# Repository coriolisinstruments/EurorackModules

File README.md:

# EurorackModules

Open-source eurorack synthesizer modules. All our schematics and pcbs are developed with [KiCad.](http://kicad.org/)

## 1U modules

These are simple (passive) utility modules, designed to fit the Intellijel 1U spec. They are often smaller (6 or 8HP) so you can use them to fill gaps in your system. Except for the Multibus... that one takes up an entire row.

| | Module | Description |
| --- | :----- | :---------- |
|| [LPG](1Utilities/1U_LPG) | A simple passive low-pass gate with -6dB slope in a small 1U package. |
|| [Mute](1Utilities/1U_Mute) | A signal mute (momentary and latching) in a convenient 1U package.|
|| [Mult](1Utilities/1U_Mult) | Dead simple passive multi. Its only feature being very small. |
|| [Multibus](Multibus) | A eurorack module for the distribution of CV signals. |

## Regular (3U) Modules

Just your regular sized eurorack modules.

| | Module | Description |
| --- | :----- | :---------- |
|| [Corona](Corona) | A multi purpose vacuum tube (or valve) drive module with feedback control. |

## Other stuff
| | Thing | Description |
| --- | :----- | :---------- |
|| [PSU Companion](PSUCompanion) | A companion for Bel / Condor / Power One linear power supplies. Goes inbetween the PSU and your busboards. |
|| [Making Vactrols](MakingVactrols) | A little tutorial on making your own vactrols. |

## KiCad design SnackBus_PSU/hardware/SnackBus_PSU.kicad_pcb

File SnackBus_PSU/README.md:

# SnackBus PSU

A small, easy to DIY, power supply for Eurorack modules. Designed to be used in a surplus Moog Mother-32 or DFAM skiff, utilizing the existing wall-wart and internal connector. Add some spacers as feet and you can also use it as a benchtop power supply for your eurorack breadboarding experiments.

*status:* build and tested

*current revision:* 2

## About

This power supply was design as a even lower-cost (the total cost is about €30), even smaller, alternative to the excellent Befaco LunchBus skiff PSU. In terms of circuitry, the SnackBus is almost identical. Why use this? Well, the SnackBus fits into a Moog 60 HP skiff (from the Mother-32 or DFAM), whereas the LunchBus does not.

## On power output

The DKE15A-12 converter used is capable of delivering 625mA on both +12V and -12V (a total of 1250mA). When it does so, it required 1.7A @12V (20.4W) from the wall-wart.

Note that the Moog adapter, supplied with the Mother-32 and DFAM, will only put out 1A @12V. This means that if you use this adapter, the SnackBus will only be able to output 350mA on both rails. Less if you use 

**Our recommendation: do not exceed 300mA power draw** on either rails when using the Moog-supplied adapter with the SnackBus. Otherwise buy a beefier adapter.

## BOM

| Component | Quantity    | Component     |
| :------------- | :------------- | :------------- |
| R1 | 1 | 680R ohm resistor (for +5V in LED) |
| R2 | 1 | 1k ohm resistor (for -12V LED) |
| R3 | 1 | 1k ohm resistor (for +12V LED) |
| R4 | 1 | 5k ohm resistor (for PWR IN LED) |
| R5 | 1 | 1K ohm resistor (for 5V) |
| R6 | 1 | 330R ohm resistor (for 5V) |
| D1 | 1 | 1N5402 diode |
| D2 | 1 | 1N4004 diode |
| C1 | 1 | Capacitor (ceramic or film) , 100nF (104) |
| C2 | 1 | Capacitor, Polarized (electrolytic) , 10uF |
| C3 | 1 | Capacitor, Polarized (electrolytic) , 22uF |
| J1 | 1 | 2-pin Molex connector |
| J2-J9 | 8 | 16-pin (02x08) Shrouded IDC header |
| U1 | 1 | LM317T voltage regulator |
| M1 | 1 | MeanWell DKE15A-12 DC-DC converter |

All resistors 1% metal film.

## Building order

By no means a build guide; just a suggested order to make building easier.

1. Start soldering with the resistors.
2. Then the diodes.
3. Add the shrouded box headers. Use something flat to keep them in place when you flip the board around.
4. Do the C1 capacitor next.
5. Bend the leads of the LM317T 90 degrees down (the heatsink being the downside of the regulator) where the leads become thinner. Make sure the hole in the tab and on the board align. Add the regular by soldering the leads and screwing the tab to the board with an M3 bolt and nut.
6. Add the LEDs. Use a piece of masking tape the keep them in place.
7. Drop in the regular, flip the board and solder it from the backside.
8. Add the polarized caps C2 and C3.
9. Finally, add J1: the Molex connector. Using a piece of masking tape to fixate it on the board is recommended.

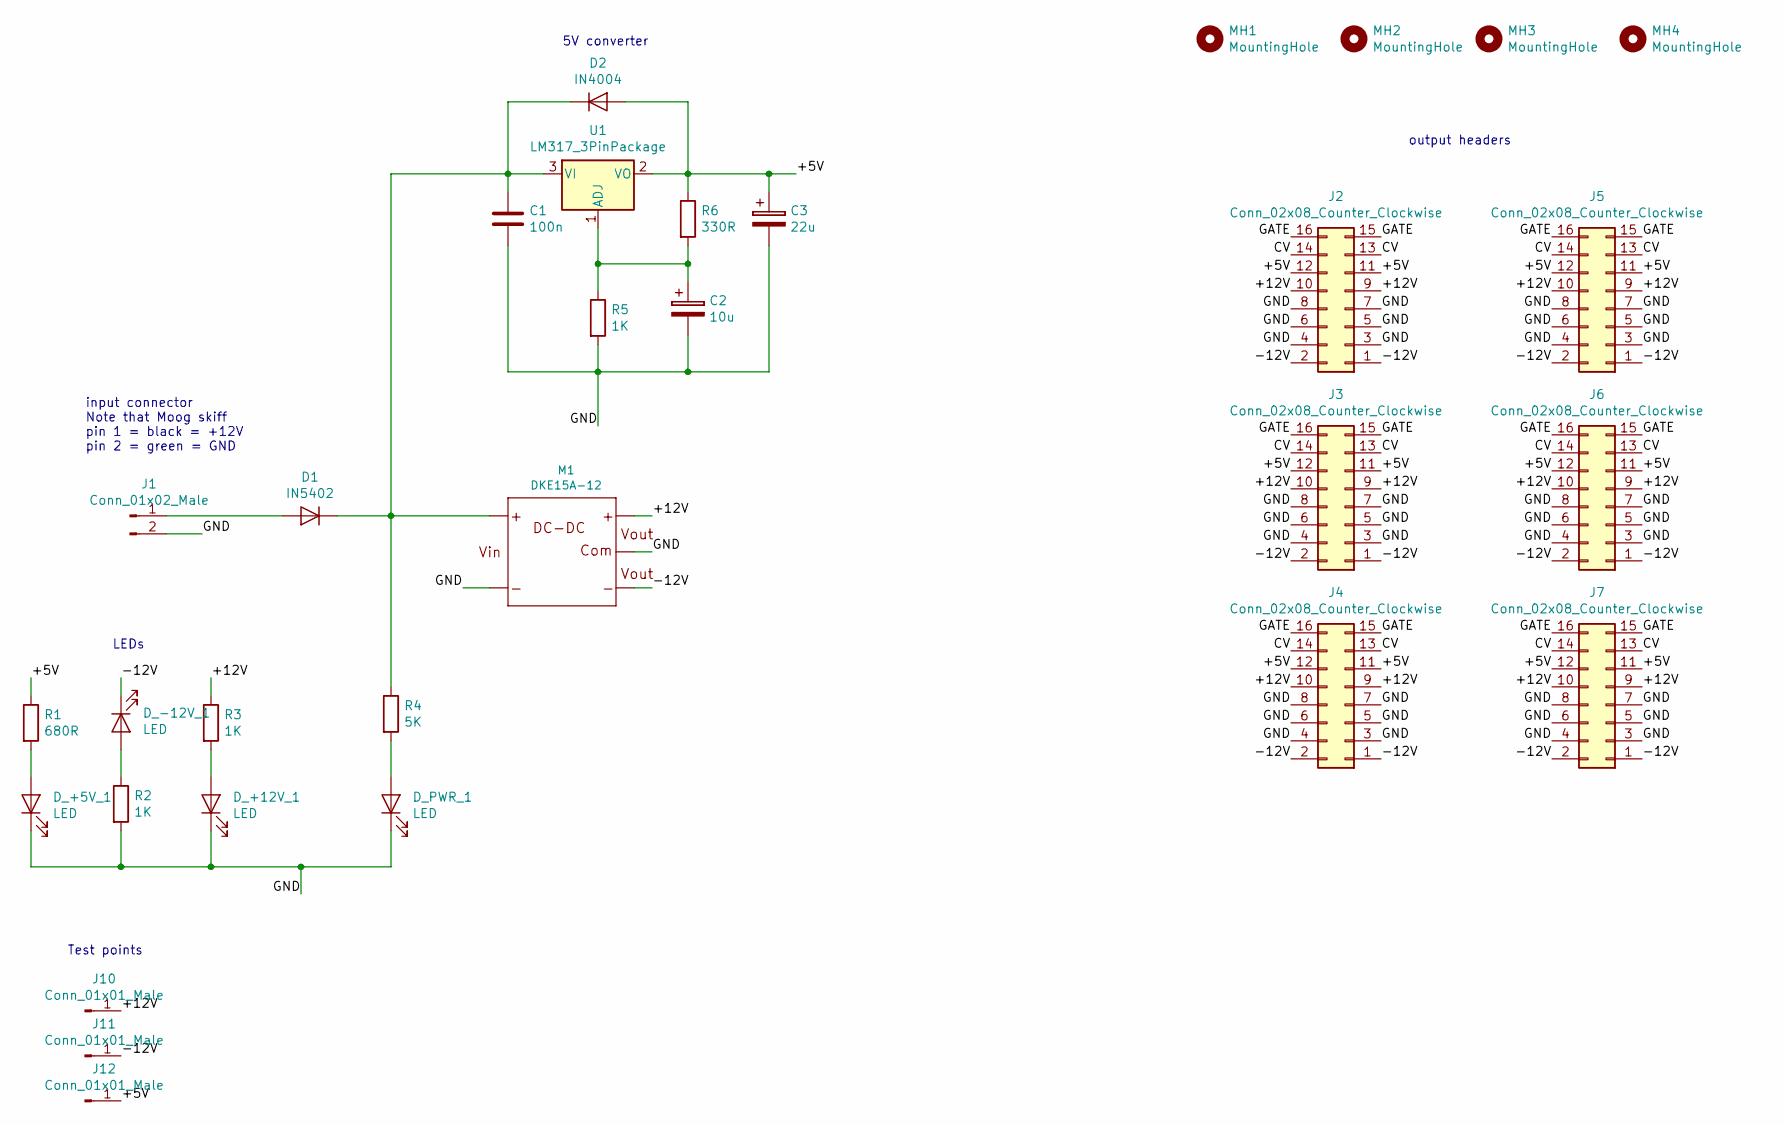
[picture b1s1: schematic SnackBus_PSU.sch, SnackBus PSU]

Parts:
C1: 100n; C_Disc_D7.0mm_W2.5mm_P5.00mm
C2: 10u; CP_Radial_D5.0mm_P2.50mm
C3: 22u; CP_Radial_D5.0mm_P2.50mm
D1: IN5402; D_DO-201AD_P15.24mm_Horizontal
D2: IN4004; D_DO-41_SOD81_P10.16mm_Horizontal
D_+5V_1, D_+12V_1: LED; LED_D3.0mm
D_-12V_1: LED; LED_D3.0mm
D_PWR_1: LED; LED_D3.0mm
J1: Conn_01x02_Male; Molex_KK-254_AE-6410-02A_1x02_P2.54mm_Vertical
J2, J3, J4, J5, J6, J7: Conn_02x08_Counter_Clockwise; IDC-Header_2x08_P2.54mm_Vertical
J10, J11, J12: Conn_01x01_Male; PinHeader_1x01_P2.54mm_Vertical
M1: DKE15A-12; MeanWell-DKE
MH1, MH2, MH3, MH4: MountingHole; MountingHole_3.2mm_M3
R1: 680R; R_Axial_DIN0207_L6.3mm_D2.5mm_P7.62mm_Horizontal
R2, R3, R5: 1K; R_Axial_DIN0207_L6.3mm_D2.5mm_P7.62mm_Horizontal
R4: 5K; R_Axial_DIN0207_L6.3mm_D2.5mm_P7.62mm_Horizontal
R6: 330R; R_Axial_DIN0207_L6.3mm_D2.5mm_P7.62mm_Horizontal
U1: LM317_3PinPackage; TO-220F-3_Horizontal_TabDown

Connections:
/+5V: C3.1, D2.2 (A), J2.11, J2.12, J3.11, J3.12, J4.11, J4.12, J5.11, J5.12, J6.11, J6.12, J7.11, J7.12, J12.1, R1.1, R6.1, U1.2 (VO); also elsewhere on the board
/+12V: J2.9, J2.10, J3.9, J3.10, J4.9, J4.10, J5.9, J5.10, J6.9, J6.10, J7.9, J7.10, J10.1, M1.3 (+VOUT), R3.1; also elsewhere on the board
/-12V: D_-12V_1.1 (K), J2.1, J2.2, J3.1, J3.2, J4.1, J4.2, J5.1, J5.2, J6.1, J6.2, J7.1, J7.2, J11.1, M1.5 (-VOUT); also elsewhere on the board
/CV: J2.13, J2.14, J3.13, J3.14, J4.13, J4.14, J5.13, J5.14, J6.13, J6.14, J7.13, J7.14; also elsewhere on the board
/GATE: J2.15, J2.16, J3.15, J3.16, J4.15, J4.16, J5.15, J5.16, J6.15, J6.16, J7.15, J7.16; also elsewhere on the board
/GND: C1.2, C2.2, C3.2, D_+5V_1.1 (K), D_+12V_1.1 (K), D_PWR_1.1 (K), J1.2, J2.3, J2.4, J2.5, J2.6, J2.7, J2.8, J3.3, J3.4, J3.5, J3.6, J3.7, J3.8, J4.3, J4.4, J4.5, J4.6, J4.7, J4.8, J5.3, J5.4, J5.5, J5.6, J5.7, J5.8, J6.3, J6.4, J6.5, J6.6, J6.7, J6.8, J7.3, J7.4, J7.5, J7.6, J7.7, J7.8, M1.2 (-VIN), M1.4 (COMMON), R2.2, R5.2; also elsewhere on the board
unnamed: C1.1, D1.1 (K), D2.1 (K), M1.1 (+VIN), R4.1, U1.3 (VI)
unnamed: C2.1, R5.1, R6.2, U1.1 (ADJ)
unnamed: D1.2 (A), J1.1
unnamed: D_+5V_1.2 (A), R1.2
unnamed: D_+12V_1.2 (A), R3.2
unnamed: D_-12V_1.2 (A), R2.1
unnamed: D_PWR_1.2 (A), R4.2

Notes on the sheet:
output headers
input connector Note that Moog skiff pin 1 = black = +12V pin 2 = green = GND
5V converter
LEDs
Test points

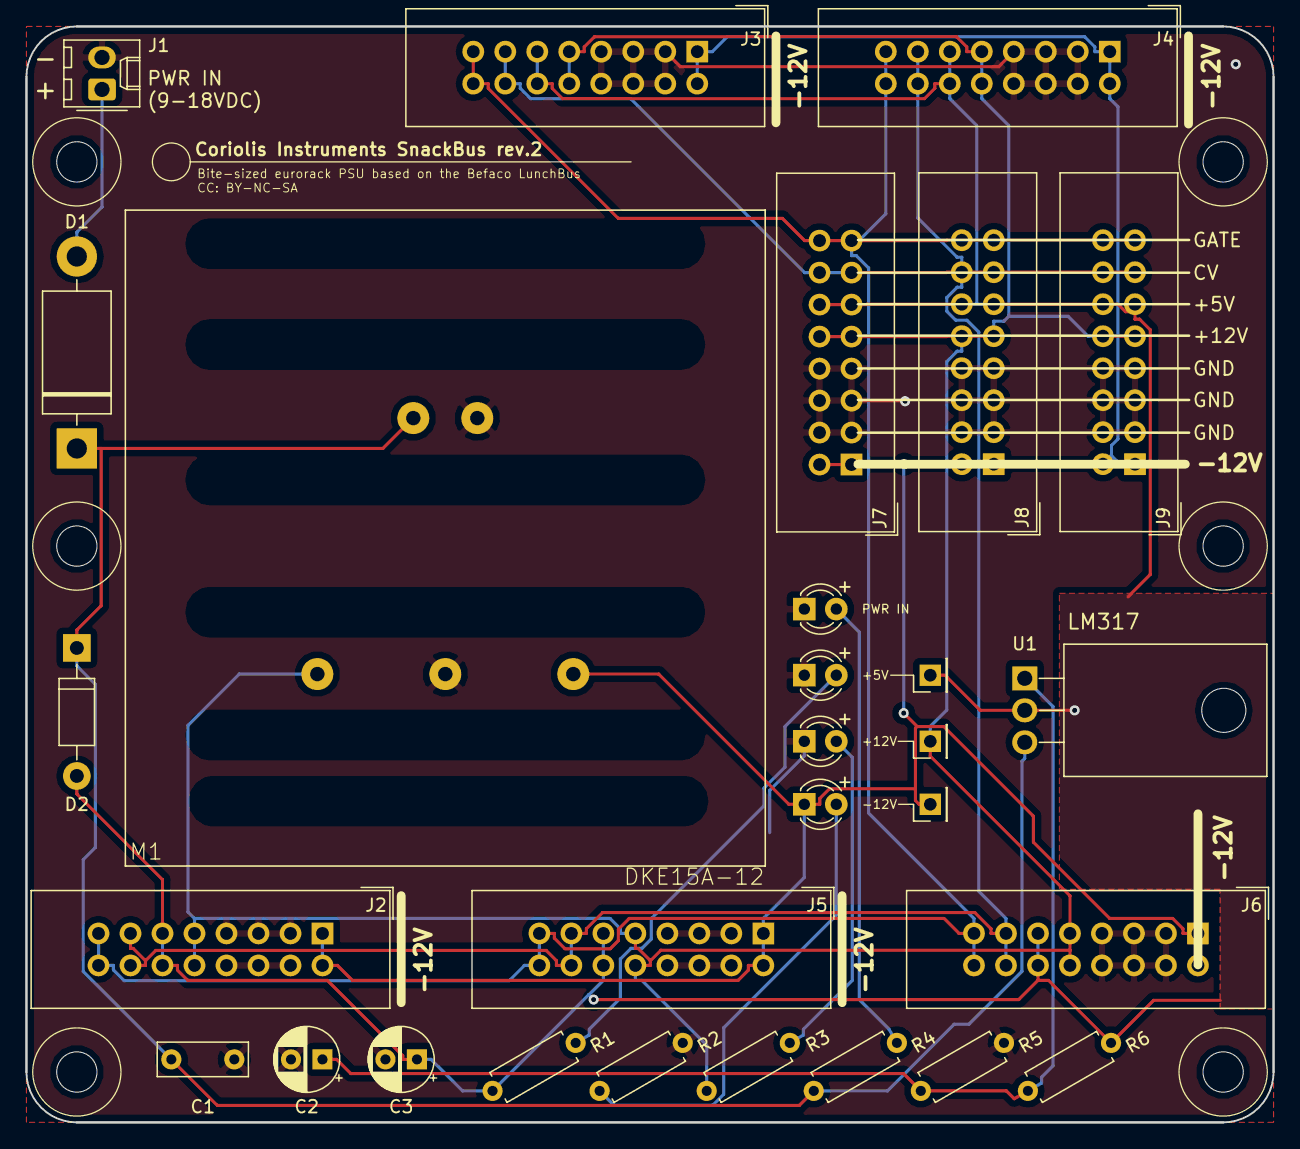
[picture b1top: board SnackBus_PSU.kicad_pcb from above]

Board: 2 copper layers, 99.0 x 87.0 mm, 41 parts (0 on the bottom side), 13 nets.

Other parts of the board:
J8, J9: Conn_02x08_Counter_Clockwise; IDC-Header_2x08_P2.54mm_Vertical
MH5, MH6: MountingHole; MountingHole_3.2mm_M3
SLOT1, SLOT2, SLOT3, SLOT4, SLOT5, SLOT6: mechanical_cooling_slot_very_large

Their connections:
/+5V: J8.11, J8.12, J9.11, J9.12; also elsewhere on the board
/+12V: J8.9, J8.10, J9.9, J9.10; also elsewhere on the board
/-12V: J8.1, J8.2, J9.1, J9.2; also elsewhere on the board
/CV: J8.13, J8.14, J9.13, J9.14; also elsewhere on the board
/GATE: J8.15, J8.16, J9.15, J9.16; also elsewhere on the board
/GND: J8.3, J8.4, J8.5, J8.6, J8.7, J8.8, J9.3, J9.4, J9.5, J9.6, J9.7, J9.8; also elsewhere on the board

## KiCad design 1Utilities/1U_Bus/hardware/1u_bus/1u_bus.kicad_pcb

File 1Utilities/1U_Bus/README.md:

# 1U Bus

Bus for the distribution of CV signals. In essence just a very big passive mult with (active) signal indicators. Basically a simplified DIY Make Noise CV bus clone.

*prototyping*

## About

Like the other modules in the 1Utilities series, this module is designed according to the [Intellijel 1U specification.](https://intellijel.com/support/1u-technical-specifications/). This one spans 104 hp width in your case.

## Remarks

It's big? There's still 4 busses with 4 in- or outputs. Like with a passive mult, any jack can be in or out; **just make sure you have one (1) and only one (!) input.** Having multiple inputs could damage your modules (connecting outputs with outputs).

Even though this module multing is passive, it still requires power to run the signal indicators. Makes for a pretty light show too. The values of the resistors in the design assume Red/Green/Blue/White leds for channels 1 to 4 respectively. You can of course substitute your own led/resistor values to taste!

## BOM

| Component | Quantity    | Component     |
| :------------- | :------------- | :------------- |
| J1 | 1 | 2x5 male header pins (2.54mm pitch), boxed or plain | 
| U1 | 1 | TL074 OpAmp |
| U2-U17 | 16 | Thonkiconn mono jacks |
| C1,C2 | 2 | 10uF (>25V) polarized capacitors |
| C3,C4 | 2 | 100nF capacitors |
| D1,D2 | 2 | 1N4001 diode|
| D_POS_?_? / D_NEG_?_? | 32 | 3mm LEDs (use same color for positive and one for negative) |
| R_Fuse_? | 1 | 10R ohm resistors |
| R_Split_?_1 | 4 | 10k ohm resistors for scaling input signal to indicator |
| R_Split_?_2 | 4 | 1k ohm resistors for scaling input signal to indicator |
| R_LED_1_? | 1 | 1k ohm resistors (depends on LEDs) |
| R_LED_2_? | 1 | 470R ohm resistors (depends on LEDs) |
| R_LED_3_? | 1 | 5k1 ohm resistors (depends on LEDs) |
| R_LED_4_? | 1 | 5k1 ohm resistors (depends on LEDs) |

## Building order

Nothing to see here yet.

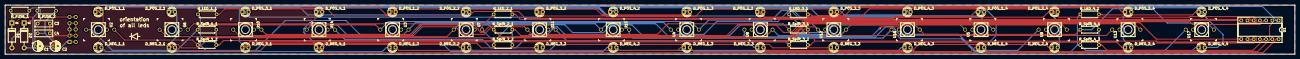
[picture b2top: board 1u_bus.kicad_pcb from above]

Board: 2 copper layers, 526.0 x 20.0 mm, 70 parts (1 on the bottom side), 49 nets.

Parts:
C1, C2: 10uF (25V); CP_Radial_D4.0mm_P2.00mm
C3, C4: 100nF; C_Disc_D7.0mm_W2.5mm_P5.00mm
D1, D2: IN4001; D_DO-41_SOD81_P10.16mm_Horizontal
D_NEG_1_1, D_NEG_1_2, D_NEG_1_3, D_NEG_1_4, D_NEG_2_1, D_NEG_2_2, D_NEG_2_3, D_NEG_2_4, D_NEG_3_1, D_NEG_3_2, D_NEG_3_3, D_NEG_3_4, D_NEG_4_1, D_NEG_4_2, D_NEG_4_3, D_NEG_4_4: LED; LED_D3.0mm
D_POS_1_1, D_POS_1_2, D_POS_1_3, D_POS_1_4, D_POS_2_1, D_POS_2_2, D_POS_2_3, D_POS_2_4, D_POS_3_1, D_POS_3_2, D_POS_3_3, D_POS_3_4, D_POS_4_1, D_POS_4_2, D_POS_4_3, D_POS_4_4: LED; LED_D3.0mm
J1: Conn_02x05_Odd_Even; PinHeader_2x05_P2.54mm_Vertical
R_FUSE_1, R_FUSE_2: 10R; R_Axial_DIN0207_L6.3mm_D2.5mm_P7.62mm_Horizontal
R_LED_1_1: 1K; R_Axial_DIN0207_L6.3mm_D2.5mm_P7.62mm_Horizontal
R_LED_2_1: 470R; R_Axial_DIN0207_L6.3mm_D2.5mm_P7.62mm_Horizontal
R_LED_3_1, R_LED_4_1: 5K1; R_Axial_DIN0207_L6.3mm_D2.5mm_P7.62mm_Horizontal
R_Split_1_1, R_Split_2_1, R_Split_3_1, R_Split_4_1: 10K; R_Axial_DIN0207_L6.3mm_D2.5mm_P7.62mm_Horizontal
R_Split_1_2, R_Split_2_2, R_Split_3_2, R_Split_4_2: 1K; R_Axial_DIN0207_L6.3mm_D2.5mm_P7.62mm_Horizontal
U1: TL074; DIP-14_W7.62mm_Socket
U2, U3, U4, U5, U6, U7, U8, U9, U10, U11, U12, U13, U14, U15, U16, U17: THONKICONNNEW; MusicThingModular-WQP-PJ301M-12_JACK

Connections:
/+12V: C1.1, C3.1, R_FUSE_1.1
/-12V: C2.2, C4.2, R_FUSE_2.1
/GND: C1.2, C2.1, C3.2, C4.1, D1.2, D2.1, J1.3, J1.4, J1.5, J1.6, J1.7, J1.8
/cv_bus1/GND: R_LED_1_1.1, R_Split_1_2.1, U2.P$3_SLEEVE, U3.P$3_SLEEVE, U4.P$3_SLEEVE, U5.P$3_SLEEVE
/cv_bus2/GND: R_LED_2_1.1, R_Split_2_2.1, U6.P$3_SLEEVE, U7.P$3_SLEEVE, U8.P$3_SLEEVE, U9.P$3_SLEEVE
/cv_bus3/GND: R_LED_3_1.1, R_Split_3_2.1, U10.P$3_SLEEVE, U11.P$3_SLEEVE, U12.P$3_SLEEVE, U13.P$3_SLEEVE
/cv_bus4/GND: R_LED_4_1.1, R_Split_4_2.1, U14.P$3_SLEEVE, U15.P$3_SLEEVE, U16.P$3_SLEEVE, U17.P$3_SLEEVE
unnamed: D1.1, J1.9, J1.10, R_FUSE_1.2
unnamed: D2.2, J1.1, J1.2, R_FUSE_2.2
unnamed: D_NEG_1_1.1, D_POS_1_1.2, U1.1
unnamed: D_NEG_1_1.2, D_NEG_1_2.1
unnamed: D_NEG_1_2.2, D_NEG_1_3.1
unnamed: D_NEG_1_3.2, D_NEG_1_4.1
unnamed: D_NEG_1_4.2, D_POS_1_4.1, R_LED_1_1.2, U1.2
unnamed: D_NEG_2_1.1, D_POS_2_1.2, U1.7
unnamed: D_NEG_2_1.2, D_NEG_2_2.1
unnamed: D_NEG_2_2.2, D_NEG_2_3.1
unnamed: D_NEG_2_3.2, D_NEG_2_4.1
unnamed: D_NEG_2_4.2, D_POS_2_4.1, R_LED_2_1.2, U1.6
unnamed: D_NEG_3_1.1, D_POS_3_1.2, U1.8
unnamed: D_NEG_3_1.2, D_NEG_3_2.1
unnamed: D_NEG_3_2.2, D_NEG_3_3.1
unnamed: D_NEG_3_3.2, D_NEG_3_4.1
unnamed: D_NEG_3_4.2, D_POS_3_4.1, R_LED_3_1.2, U1.9
unnamed: D_NEG_4_1.1, D_POS_4_1.2, U1.14
unnamed: D_NEG_4_1.2, D_NEG_4_2.1
unnamed: D_NEG_4_2.2, D_NEG_4_3.1
unnamed: D_NEG_4_3.2, D_NEG_4_4.1
unnamed: D_NEG_4_4.2, D_POS_4_4.1, R_LED_4_1.2, U1.13
unnamed: D_POS_1_1.1, D_POS_1_2.2
unnamed: D_POS_1_2.1, D_POS_1_3.2
unnamed: D_POS_1_3.1, D_POS_1_4.2
unnamed: D_POS_2_1.1, D_POS_2_2.2
unnamed: D_POS_2_2.1, D_POS_2_3.2
unnamed: D_POS_2_3.1, D_POS_2_4.2
unnamed: D_POS_3_1.1, D_POS_3_2.2
unnamed: D_POS_3_2.1, D_POS_3_3.2
unnamed: D_POS_3_3.1, D_POS_3_4.2
unnamed: D_POS_4_1.1, D_POS_4_2.2
unnamed: D_POS_4_2.1, D_POS_4_3.2
unnamed: D_POS_4_3.1, D_POS_4_4.2
unnamed: R_Split_1_1.1, U2.P$1_TIP, U3.P$1_TIP, U4.P$1_TIP, U5.P$1_TIP
unnamed: R_Split_1_1.2, R_Split_1_2.2, U1.3
unnamed: R_Split_2_1.1, U6.P$1_TIP, U7.P$1_TIP, U8.P$1_TIP, U9.P$1_TIP
unnamed: R_Split_2_1.2, R_Split_2_2.2, U1.5
unnamed: R_Split_3_1.1, U10.P$1_TIP, U11.P$1_TIP, U12.P$1_TIP, U13.P$1_TIP
unnamed: R_Split_3_1.2, R_Split_3_2.2, U1.10
unnamed: R_Split_4_1.1, U14.P$1_TIP, U15.P$1_TIP, U16.P$1_TIP, U17.P$1_TIP
unnamed: R_Split_4_1.2, R_Split_4_2.2, U1.12

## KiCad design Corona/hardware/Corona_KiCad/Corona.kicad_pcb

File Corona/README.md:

# Corona
A multi purpose vacuum tube (or valve) drive module with feedback control.

status: prototyping (2018.02.10)

## About
This design is based on Matsumin's well-known "Valvecaster" guitar stompbox design for 12A*7 tubes. This module can act as a regular tube amp with low gain tubes such as the 12AU7. Because the maximum plate voltage is limited to 24V, higher gain tubes are "starved" which introduces distorts the sound in a typical way. The higher the gain, the more pronounced this effect is.

The module consists of 2 boards:
- Tube board that holds (and powers) the actual tube,
- Main board that holds the jacks, pots and the actual drive circuit.

## Tube board
The tube board is connected to the main board via a short (eurorack-standard) 10-pin ribbon cable and incorporates a 6.3V regulator. A jumper on the back of the board allows to select the voltage for the heating filaments. This means the module can also work with the pin-compatible 6N2P (aka 6H2N) Russian model tube, which only differs from the 12A*7 tubes in the voltage needed for earlier mentioned heating filaments (pin 4 and 5).

## Main board
The audio that travels through the circuitry on the main board experiences 5 stages:
- Adjustable input gain (max. +6dB),
- Tube drive,
- Tone filter,
- Adjustable output gain (max. +50dB which puts a 12AX7 in self-oscillation), and
- Adjustable feedback.

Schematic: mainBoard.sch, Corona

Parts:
C1, C2: 47nF; C_Rect_L7.0mm_W2.5mm_P5.00mm
C3, C4: 10uF (25V); CP_Radial_D4.0mm_P2.00mm
C5, C6, C8: 100nF; C_Rect_L7.0mm_W2.5mm_P5.00mm
C7, C12: 1uF (25V); CP_Radial_D4.0mm_P2.00mm
C9: 22nF; C_Rect_L7.0mm_W2.5mm_P5.00mm
C10: 0.22uF; CP_Radial_D4.0mm_P2.00mm
D1, D2: IN4001; D_DO-41_SOD81_P10.16mm_Horizontal
D3, D4, D5: IN4148; D_DO-35_SOD27_P7.62mm_Horizontal
D6, D7: LED; LED_D3.0mm
F1, F2: 72V/0.25A; Fuse_TE5_Littlefuse-395Series
J1, J3: Conn_02x05_Odd_Even; Pin_Header_Straight_2x05_Pitch2.54mm
J_IN1: Audio-Jack-2_Switch; WQP-PJ301M-12_JACK
J_OUT1: Audio-Jack-2_Switch; WQP-PJ301M-12_JACK
MK3, MK4: Mounting_Hole; MountingHole_3.2mm_M3
Q1, Q3, Q4: BC547; TO-92_Molded_Narrow
Q2: BC557; TO-92_Molded_Narrow
R1, R6: 1M; R_Axial_DIN0207_L6.3mm_D2.5mm_P7.62mm_Horizontal
R2: 220K; R_Axial_DIN0207_L6.3mm_D2.5mm_P7.62mm_Horizontal
R3: 470K; R_Axial_DIN0207_L6.3mm_D2.5mm_P7.62mm_Horizontal
R4, R16, R26, R27: 100K; R_Axial_DIN0207_L6.3mm_D2.5mm_P7.62mm_Horizontal
R5: 47K; R_Axial_DIN0207_L6.3mm_D2.5mm_P7.62mm_Horizontal
R7, R14, R17, R42: 10K; R_Axial_DIN0207_L6.3mm_D2.5mm_P7.62mm_Horizontal
R8, R18: 5K; R_Axial_DIN0207_L6.3mm_D2.5mm_P7.62mm_Horizontal
R9, R25, R40, R41: 1K; R_Axial_DIN0207_L6.3mm_D2.5mm_P7.62mm_Horizontal
R19: 470r; R_Axial_DIN0207_L6.3mm_D2.5mm_P7.62mm_Horizontal
RV_GAIN1: A500K; 9MM_SNAP-IN_POT
RV_IN1: 100K; 9MM_SNAP-IN_POT
SW1: SW_SPDT; SUBMINI_TOGGLE
U1: TL074; DIP-14_W7.62mm_Socket
U5, U6: VTL5C; PerkinElmer_VTL5C

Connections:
/Main board/+12V: C3.1, C5.1, D3.2 (A), F1.1, J3.9, Q1.1 (C), Q3.1 (C), R2.2, R4.2, U1.4 (V+); also elsewhere on the board
/Main board/-12V: C4.2, C6.2, F2.1, J3.10, SW1.3 (C), U1.11 (V-); also elsewhere on the board
/Main board/AUDIO_OUT: C8.2, J3.5, R19.2, U1.13 (-), U1.14
/Main board/CV_DRV: U5.2; also elsewhere on the board
/Main board/CV_FB: R6.1; also elsewhere on the board
/Main board/CV_TONE: U6.2; also elsewhere on the board
/Main board/GND: C3.2, C4.1, C5.2, C6.1, C10.2, D1.2 (A), D2.1 (K), J1.3, J1.4, J1.5, J1.6, J1.7, J1.8, J3.4, J_IN1.2, J_OUT1.2, R7.2, R8.1, R16.1, R18.1, R25.1, R26.1, R27.1, RV_IN1.1, SW1.1 (A), U1.5 (+), U1.10 (+), U6.3; also elsewhere on the board
/Main board/TUBE_1: C2.2, J3.1, R2.1
/Main board/TUBE_2: C1.1, J3.2, R1.2
/Main board/TUBE_3: J3.3, U5.4
/Main board/TUBE_6: C7.1, J3.6, R4.1
/Main board/TUBE_7: C2.1, J3.7, R3.2
/Main board/TUBE_8: J3.8, R1.1, R3.1, SW1.2 (B), U5.3
/Main board/TUBE_IN: C1.2, C9.2, R42.1, U1.1
/Main board/TUBE_OUT: C12.2, R14.2, R40.2
unnamed: C7.2, R9.2
unnamed: C8.1, U6.4
unnamed: C9.1, D7.2 (A), Q4.3 (E), R25.2
unnamed: C10.1, Q1.3 (E), R16.2, R17.2
unnamed: C12.1, RV_GAIN1.1, U1.8
unnamed: D1.1 (K), F1.2, J1.9, J1.10
unnamed: D2.2 (A), F2.2, J1.1, J1.2
unnamed: D3.1 (K), D4.2 (A)
unnamed: D4.1 (K), D5.2 (A)
unnamed: D5.1 (K), D6.2 (A), Q2.3 (E)
unnamed: D6.1 (K), Q2.1 (C), R18.2
unnamed: D7.1 (K), R8.2
unnamed: J_IN1.1, R5.2
unnamed: J_OUT1.1, R19.1
unnamed: Q1.2 (B), R14.1
unnamed: Q2.2 (B), R17.1
unnamed: Q3.2 (B), R6.2
unnamed: Q3.3 (E), Q4.2 (B)
unnamed: Q4.1 (C), R41.1, U1.7, U1.12 (+)
unnamed: R5.1, RV_IN1.3
unnamed: R9.1, RV_GAIN1.2, RV_GAIN1.3, U1.9 (-)
unnamed: R26.2, U6.1
unnamed: R27.2, U5.1
unnamed: R40.1, R41.2, U1.6 (-)
unnamed: R7.1, R42.2, U1.2 (-)
unnamed: RV_IN1.2, U1.3 (+)

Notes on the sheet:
Reverse polarity protection with input power buffers.
Powersupply
Connection to tube board
OVERVIEW
After-tube gain circuit Gain = 1 + (R7/R6) ie. now limited to 1+(500k/1k) = 501 = 50+ dB!!!
TUBE OVERDRIVE
Clipping indicator
Suggested R values: red/green/amber - 5K blue/white/pink - 10K
Plate voltage switch This switches the ground of the tube section (grid drain+cathode) to 1) Up = -12V for 24V Vp or 2) Down = GND for regular 12V Vp
high-pass: f = 1/(2pi*R1*C1) = 1/(6.28*470k*47n*) = 7.2 Hz
3=up
Feedback control Uses 0-12V. Somehow this seems to work. #noclue
Feedback indicator 1K used as pull down to dim LED when gain is set to 0
Tone (-3dB low-pass)
Buffer and invert back
For mounting the tube board to the front panel with spacers (the tube needs to sit recessed)

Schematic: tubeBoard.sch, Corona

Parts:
D_TUBE1: LED; LED_D3.0mm
J2, J6: Conn_01x03_Male; Pin_Header_Straight_1x03_Pitch2.54mm
J4: Conn_02x05_Odd_Even; Pin_Header_Straight_2x05_Pitch2.54mm
J5: Conn_01x02_Male; PinHeader_1x02_P2.54mm_Vertical
MK1, MK2: Mounting_Hole; MountingHole_3.2mm_M3
R23: 1K; R_Axial_DIN0207_L6.3mm_D2.5mm_P7.62mm_Horizontal
RFBB1: POT_TRIM; Potentiometer_Trimmer_Bourns_3296W
RFBT1: 150r; R_Axial_DIN0207_L6.3mm_D2.5mm_P7.62mm_Horizontal
SX1: VT9-PT; belton-engineering-VT9-PT
U2: LM337_TO220; TO-220-3_Vertical

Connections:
/Tube Board/-6.3V_TB: J2.3, RFBT1.2, U2.3 (VO)
/Tube Board/-12V_TB: J2.1, J4.10, U2.2 (VI)
/Tube Board/AUDIO_OUT_TB: J4.5, R23.2
/Tube Board/GND_TB: D_TUBE1.1 (K), J4.4, J6.1, RFBB1.1, RFBB1.2
/Tube Board/TUBE_1_TB: J4.1, SX1.1
/Tube Board/TUBE_2_TB: J4.2, SX1.2
/Tube Board/TUBE_3_TB: J4.3, SX1.3
/Tube Board/TUBE_4_TB: J2.2, J5.1, SX1.4
/Tube Board/TUBE_6_TB: J4.6, SX1.6
/Tube Board/TUBE_7_TB: J4.7, SX1.7
/Tube Board/TUBE_8_TB: J4.8, SX1.8
unnamed: D_TUBE1.2 (A), R23.1
unnamed: J5.2, J6.3
unnamed: J6.2, SX1.5
unnamed: RFBB1.3, RFBT1.1, U2.1 (ADJ)

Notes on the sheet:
Connection to main board !! Mirrored !!
For different tubes switch between 1) 12V (12A*7) and 3) 6.3V (6N2H) Note we use the -12V rail to balance some of the power consumption in typical a eurorack system. Hence the reversal of the connections to pin 4 and 5.
Vout = -1.25*((RFBB/RFBT) + 1) or Rfbb = Rfbt*((Vout/-1.25)-1) in our case: Rfbb = 150*((-6.25/-1.25)-1)=900r
Selectable ground for the tube plate voltage (GND or -12V). Needed for changing tube LEDs
LEDs to illuminate the tube (indicates sound)
For mounting the tube board to the front panel with spacers (the tube needs to sit recessed)
pins for external power
pins for internal/external heating power

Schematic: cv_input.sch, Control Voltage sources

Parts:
J_IN_DRV1: Audio-Jack-2_Switch; WQP-PJ301M-12_JACK
J_IN_FB1: Audio-Jack-2_Switch; WQP-PJ301M-12_JACK
J_IN_TONE1: Audio-Jack-2_Switch; WQP-PJ301M-12_JACK
R10, R11, R13, R15, R20, R21, R22, R33, R36, R37, R38, R39: 10K; R_Axial_DIN0207_L6.3mm_D2.5mm_P7.62mm_Horizontal
R12, R30, R31, R32, R34, R35: 200K; R_Axial_DIN0207_L6.3mm_D2.5mm_P7.62mm_Horizontal
RV_DRV1: 100K; 9MM_SNAP-IN_POT
RV_DRV_CV1: 100K; 9MM_SNAP-IN_POT
RV_FB1: 100K; 9MM_SNAP-IN_POT
RV_FB_CV1: 100K; 9MM_SNAP-IN_POT
RV_TONE1: 100K; 9MM_SNAP-IN_POT
RV_TONE_CV1: 100K; 9MM_SNAP-IN_POT
U3: TL074; DIP-14_W7.62mm_Socket
U4: TL072; DIP-8_W7.62mm_Socket

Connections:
/Main board/+12V: RV_DRV1.3, RV_FB1.3, RV_TONE1.3, U3.4 (V+), U4.8 (V+); also elsewhere on the board
/Main board/-12V: U3.11 (V-), U4.4 (V-); also elsewhere on the board
/Main board/CV_DRV: R21.1, U3.7; also elsewhere on the board
/Main board/CV_FB: R22.1, U3.1; also elsewhere on the board
/Main board/CV_TONE: R39.1, U4.7; also elsewhere on the board
/Main board/GND: J_IN_DRV1.2, J_IN_FB1.2, J_IN_TONE1.2, R15.1, R20.1, R38.1, RV_DRV1.1, RV_DRV_CV1.1, RV_FB1.1, RV_FB_CV1.1, RV_TONE1.1, RV_TONE_CV1.1; also elsewhere on the board
unnamed: J_IN_DRV1.1, R30.2, RV_DRV_CV1.3
unnamed: J_IN_FB1.1, R12.2, RV_FB_CV1.3
unnamed: J_IN_TONE1.1, R34.2, RV_TONE_CV1.3
unnamed: R10.1, R11.1, U3.5 (+)
unnamed: R10.2, R31.1, U3.8
unnamed: R11.2, RV_DRV1.2
unnamed: R12.1, R32.2, U3.13 (-)
unnamed: R13.1, R33.1, U3.3 (+)
unnamed: R13.2, RV_FB1.2
unnamed: R15.2, R21.2, U3.6 (-)
unnamed: R20.2, R22.2, U3.2 (-)
unnamed: R30.1, R31.2, U3.9 (-)
unnamed: R32.1, R33.2, U3.14
unnamed: R34.1, R35.2, U4.2 (-)
unnamed: R35.1, R37.2, U4.1
unnamed: R36.1, R37.1, U4.5 (+)
unnamed: R36.2, RV_TONE1.2
unnamed: R38.2, R39.2, U4.6 (-)
unnamed: RV_DRV_CV1.2, U3.10 (+)
unnamed: RV_FB_CV1.2, U3.12 (+)
unnamed: RV_TONE_CV1.2, U4.3 (+)

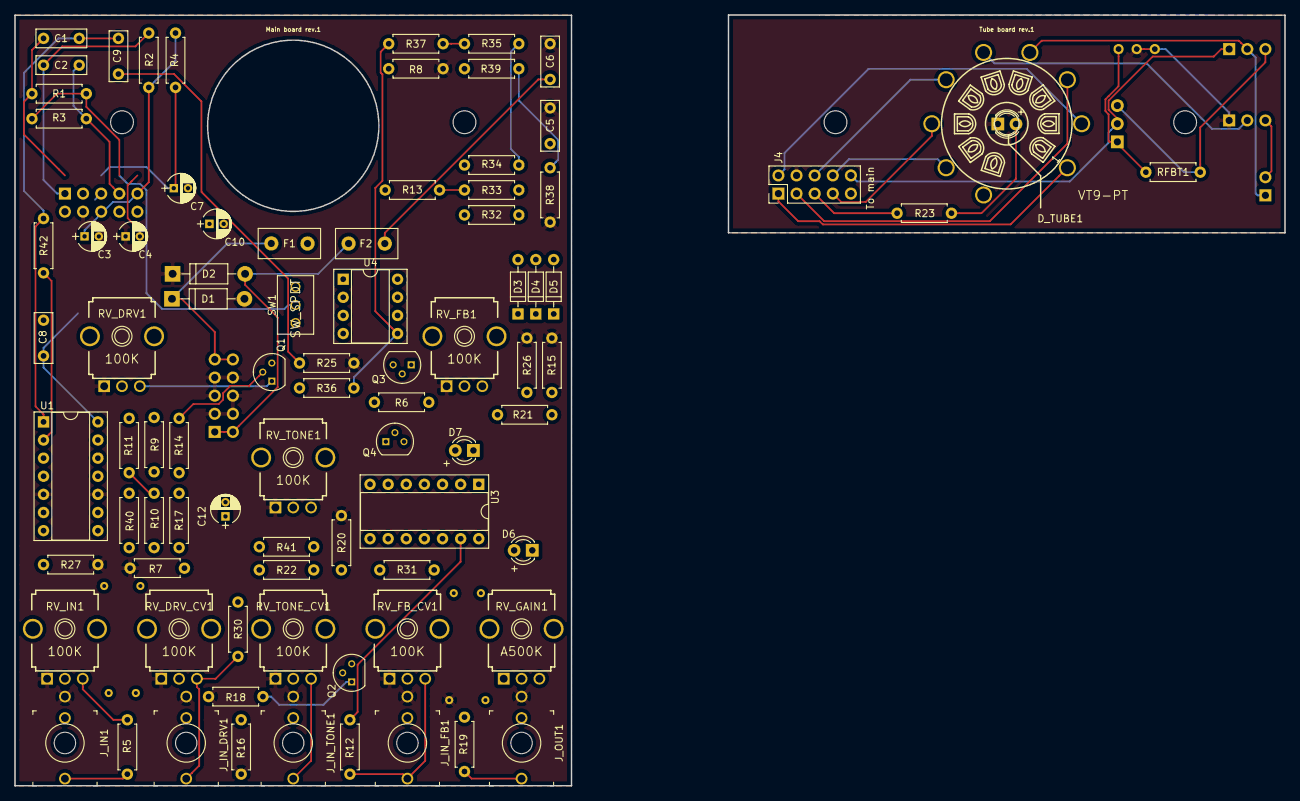
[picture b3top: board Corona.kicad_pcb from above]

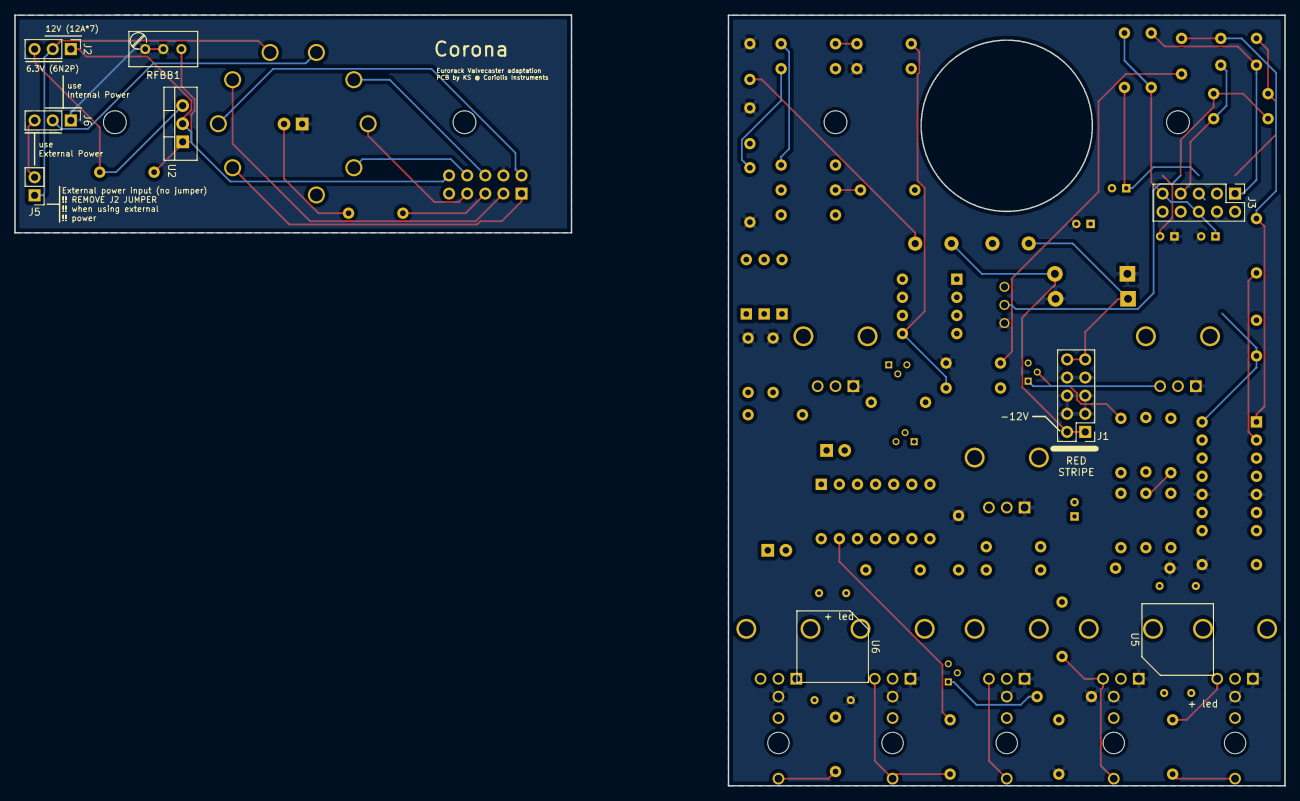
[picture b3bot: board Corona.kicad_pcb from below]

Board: 2 copper layers, 78.0 x 108.0 mm, 97 parts (10 on the bottom side), 77 nets.

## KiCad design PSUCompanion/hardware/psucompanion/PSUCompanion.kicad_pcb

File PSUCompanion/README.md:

# PSU Companion

A companion board designed for Bel / Condor / Power One linear power supplies. Goes inbetween the power supply unit (PSU) and your busboards. Might be useful for other kinds of power supplies too.

status: build and working

## About
Why does this thing exist? Well, this board combines several simple functions in one package. However it's primarily intended for delaying the load on the power supply. In this particular case that means delaying the coupling of busboards (and thus modules) to the supply. Hence this thing sits between the PSU and busboards.

Because we made this anyway, we threw in:
- A simple 5V power supply,
- Easier hook-up for busboards to the PSU.

### Delayed Coupling (or power sequencing)

Why delay putting load on the PSU? 

We've observed when using a Bel HBB15-1.5AG PSU in combination with a Moog DFAM module some unpredictable start-up behaviour can occur. This is primarily noticable with the +12V rail which in some cases does not deliver +12V but rather +3V. Sometimes turning the power off and on fixes this, and sometimes it doesn't. 

Most likely the power supply's protection kicks in because of a spike in current demand from the modules (especially modules with a larger power consumption) __in combination__ with the cold power supply (empty capacitors). People have observed the same thing with Moog Mother 32's.

Delaying the coupling of the modules ensures the power supply itself is properly up and running before load is put upon it. This fixes the unreliable power up in combination with the DFAM. The delay time with specified components is about 0.5s (C3 = 47uF) and depends on the value of capacitor C3 (larger capacity = longer delay; eg. 100uF -> about 1s delay).

### 5V power supply

The aforementioned linear power supplies typically come with only + and - 12V (or 15V) outputs. 
This is a simple 5V supply based on the LM317T voltage regulator to add 5V to the system. The theoretical maximum load is 1.5A, but this design assumes a light load of no more than 150mA. This means a small heatsink suffices and the amount of current 'stolen' from the +12V is limited.

The supply can be disabled by removing jumper J6 (this disconnects the +12V input) if more headroom on the +12V rail is needed.

### Distribution of power

Every output (after the relay) is accessible through a 3-pole terminal block. This allows for connections to (for example) 2 busboards and some status LEDs without the need for soldering wires together. Looks nicer and is a little easier to troubleshoot.

## Remarks

Note 1: keeping the relay open requires power. The Panasonic JW2SN12 in the design consumes 44mA while opened. This should not pose a problem as the coil is powered from the -12V rail. In most eurorack systems, this is the rail with the lowest load.

Note 2: delaying the load on the supply does not mean the current is limited. When the total power consumption of modules approaches the PSU limit, you could still get dropouts as the peak current draw might still be too large for the supply. This behaviour is dependent on the modules you have installed.

## BOM

| Component | Quantity    | Component     |
| :------------- | :------------- | :------------- |
| R1 | 1 | 150k ohm resistor |
| R2 | 1 | 20k ohm resistor (limits the current flow to C3) |
| R3 | 1 | 20k ohm resistor |
| R4 | 1 | 1k ohm resistor (for 5V) |
| R5 | 1 | 330R ohm resistor (for 5V) |
| D1 | 1 | 1N4001 diode |
| D2 | 1 | 1N4007 diode |
| C1,C2 | 2 | Capacitor (ceramic or film) , 100nF (104) |
| C3 | 1 | Capacitor, Polarized (electrolytic) , 47uF - 100uF |
| Q1 | 1 | NPN transistor, EBC (eg. 2N3904 or 2N2222; you can also use a CBE like the BC547; just make sure to flip it around on the board). |
| J? | 5 | 3 pole screw terminal blocks with 5.00mm pin spacing (eg. Deca MB310); possibly 5.08mm (0.200") spacing could also fit |
| J6 | 1 | 2 pin header (with jumper) or bridged with a resistor leg (permanent) |
| U1 | 1 | LM317T voltage regulator |
| RL1 | 1 | Panasonic JW2SN12 DPDT relay |

All resistors 1% metal film.

## Building order

By no means a build guide; just a suggested order to make building easier.

1. Start soldering with the resistors.
2. Then the diodes.
3. Do the capacitors next.
4. Add the transistor.
5. Put a 1x2 pin header on J6 or make a permanent connection by bridging the connection with a piece of excess resistor leg (you'll probably have some clippings around from R1-5).
6. Add the terminal blocks and flip the whole thing over and solder them. This works best if the board is resting one the terminal blocks on a flat surface.
7. Mount the heatsink to the LM317T if you haven't already and solder it to the board. 
8. Finally, solder the relay in place.

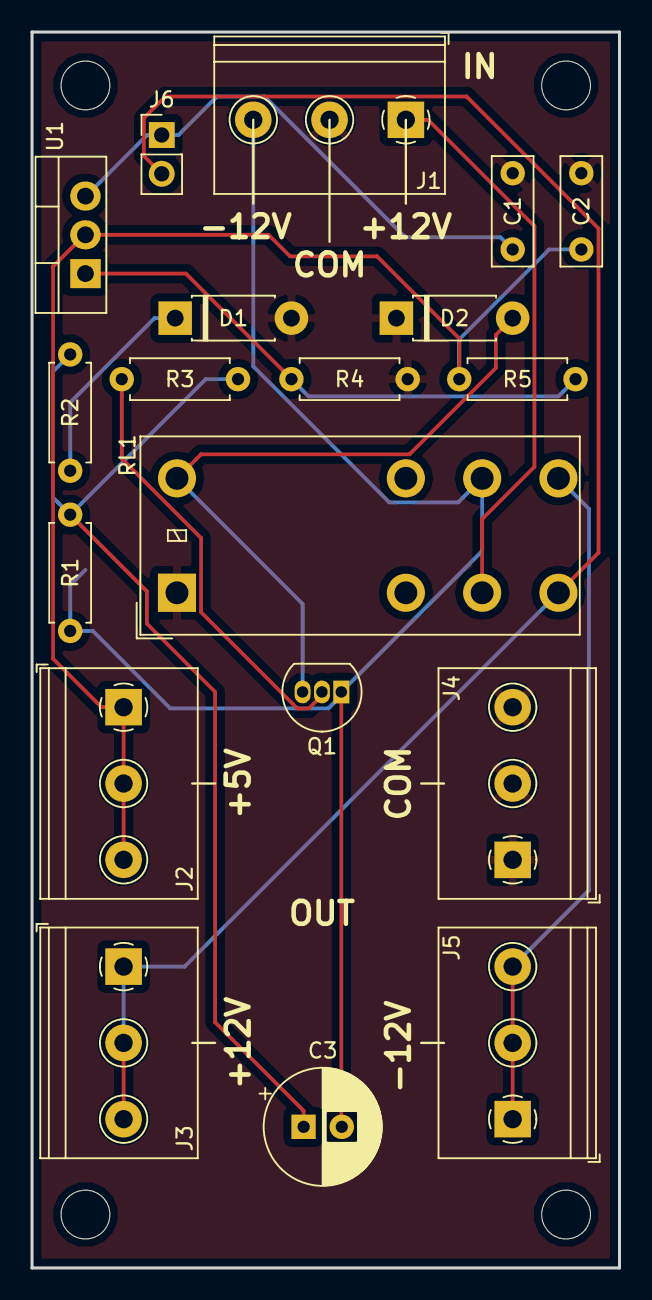
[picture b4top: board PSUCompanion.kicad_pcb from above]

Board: 2 copper layers, 38.5 x 81.0 mm, 23 parts (0 on the bottom side), 12 nets.

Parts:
C1, C2: 100n; C_Disc_D7.0mm_W2.5mm_P5.00mm
C3: 100uF; CP_Radial_D7.5mm_P2.50mm
D1: IN4001; D_DO-41_SOD81_P7.62mm_Horizontal
D2: IN4007; D_DO-41_SOD81_P7.62mm_Horizontal
J1, J2, J3, J4, J5: Conn_01x03_Male; TerminalBlock_Philmore_TB133_1x03_P5.00mm_Horizontal
J6: Conn_01x02_Male; PinHeader_1x02_P2.54mm_Vertical
MH1, MH2, MH3, MH4: MountingHole; MountingHole_3.2mm_M3
Q1: 2N3904; TO-92_Inline
R1: 150K; R_Axial_DIN0207_L6.3mm_D2.5mm_P7.62mm_Horizontal
R2, R3: 20K; R_Axial_DIN0207_L6.3mm_D2.5mm_P7.62mm_Horizontal
R4: 1K; R_Axial_DIN0207_L6.3mm_D2.5mm_P7.62mm_Horizontal
R5: 330R; R_Axial_DIN0207_L6.3mm_D2.5mm_P7.62mm_Horizontal
RL1: JW2; Relay_DPDT_Panasonic_JW2
U1: LM317_3PinPackage; TO-220-3_Vertical

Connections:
/+5_out: C2.1, J2.1, J2.2, J2.3, R5.1, U1.2
/+12_in: J1.1, RL1.3
/+12_out: J3.1, J3.2, J3.3, J6.2, RL1.4
/-12_in: C3.2, J1.3, Q1.1, R1.1, RL1.6
/-12_out: J5.1, J5.2, J5.3, RL1.5
/COM: C1.2, C2.2, D1.2, D2.1, J1.2, J4.1, J4.2, J4.3, R4.2, RL1.1
unnamed: C1.1, J6.1, U1.3
unnamed: C3.1, R1.2, R2.1, R3.2
unnamed: D1.1, R2.2
unnamed: D2.2, Q1.3, RL1.8
unnamed: Q1.2, R3.1
unnamed: R4.1, R5.2, U1.1

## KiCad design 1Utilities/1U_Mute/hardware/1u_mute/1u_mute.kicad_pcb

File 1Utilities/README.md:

# 1Utilities

These are simple (passive) utility modules, designed to fit the Intellijel 1U spec. They are often smaller (6 or 8HP; except the bus.. that thing is huge) so you can use them to fill gaps in your system.

| Module | Description |
| :----- | :---------- |
| [Bus](1U_Bus) | Bus for the distribution of CV signals.  |
| [LPG](1U_LPG) | A simple passive low-pass gate with -6dB slope in a small 1U package. |
| [Mute](1U_Mute) | A signal mute (momentary and latching) in a convenient 1U package.|
| [Mult](1U_Mult) | Dead simple passive multi. Its only feature being very small. |

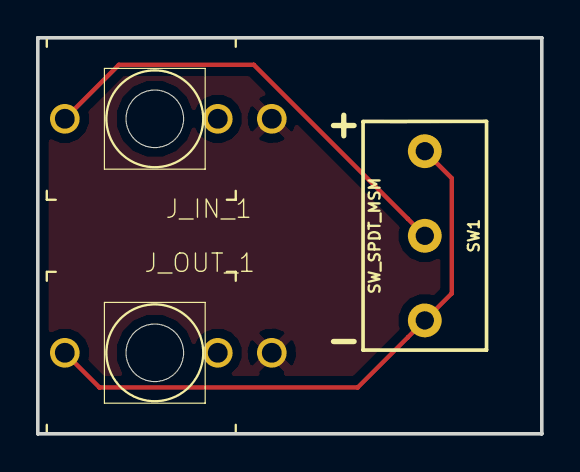
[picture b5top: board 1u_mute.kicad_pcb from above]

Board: 2 copper layers, 28.0 x 22.0 mm, 3 parts (0 on the bottom side), 3 nets.

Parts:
J_IN_1: thonkiconn; MusicThingModular-WQP-PJ301M-12_JACK
J_OUT_1: thonkiconn; MusicThingModular-WQP-PJ301M-12_JACK
SW1: SW_SPDT_MSM; Miniswitch(4.7mm)

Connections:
GND: J_IN_1.P$3_SLEEVE, J_OUT_1.P$3_SLEEVE
unnamed: J_IN_1.P$1_TIP, SW1.2
unnamed: J_OUT_1.P$1_TIP, SW1.1, SW1.3

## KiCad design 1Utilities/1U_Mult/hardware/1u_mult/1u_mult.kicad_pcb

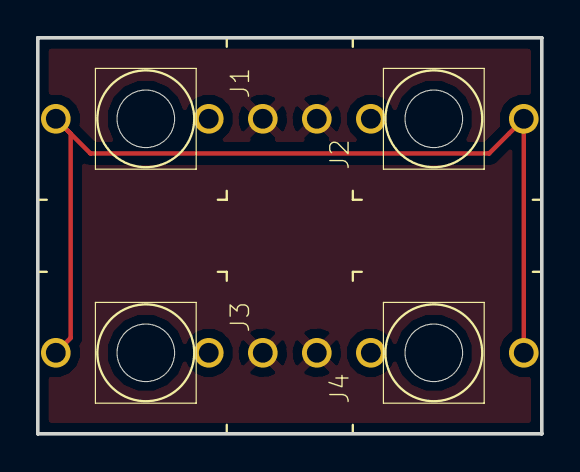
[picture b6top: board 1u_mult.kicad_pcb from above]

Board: 2 copper layers, 28.0 x 22.0 mm, 4 parts (0 on the bottom side), 2 nets.

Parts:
J1, J2, J3, J4: THONKICONNNEW; MusicThingModular-WQP-PJ301M-12_JACK

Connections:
GND: J1.P$3_SLEEVE, J2.P$3_SLEEVE, J3.P$3_SLEEVE, J4.P$3_SLEEVE
unnamed: J1.P$1_TIP, J2.P$1_TIP, J3.P$1_TIP, J4.P$1_TIP

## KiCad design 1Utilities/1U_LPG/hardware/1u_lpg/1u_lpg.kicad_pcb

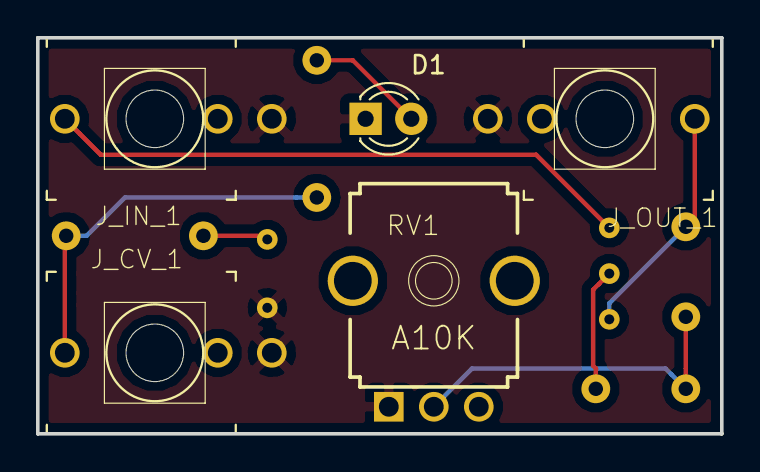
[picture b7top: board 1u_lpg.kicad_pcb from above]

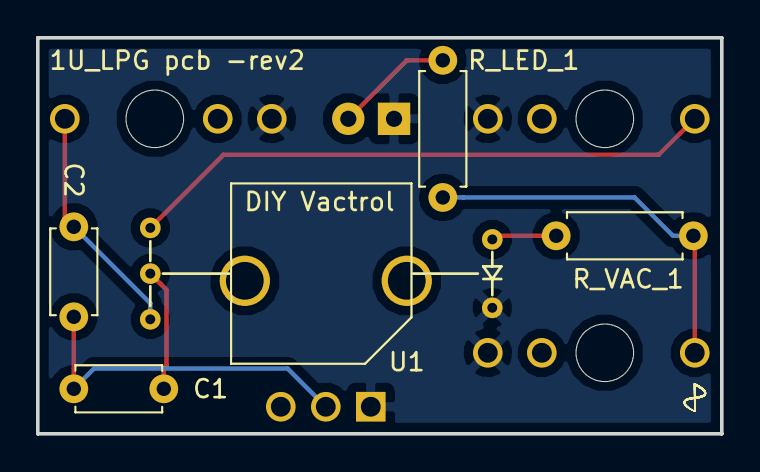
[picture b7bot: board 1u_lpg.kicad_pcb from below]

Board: 2 copper layers, 38.0 x 22.0 mm, 10 parts (5 on the bottom side), 8 nets.

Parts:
C1, C2: 0.1uF; C_Disc_D4.7mm_W2.5mm_P5.00mm
D1: LED; LED_D3.0mm
J_CV_1: thonkiconn; MusicThingModular-WQP-PJ301M-12_JACK
J_IN_1: thonkiconn; MusicThingModular-WQP-PJ301M-12_JACK
J_OUT_1: thonkiconn; MusicThingModular-WQP-PJ301M-12_JACK
RV1: A10K; MusicThingModular-9MM_SNAP-IN_POT
R_LED_1: 20K; R_Axial_DIN0207_L6.3mm_D2.5mm_P7.62mm_Horizontal
R_VAC_1: 100K; R_Axial_DIN0207_L6.3mm_D2.5mm_P7.62mm_Horizontal
U1: VTL5Cx2; DIY_Optoisolator_VTL5Cx2

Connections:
GND: D1.1, J_CV_1.P$3_SLEEVE, J_IN_1.P$3_SLEEVE, J_OUT_1.P$3_SLEEVE, RV1.1, U1.1
unnamed: C1.1, U1.4
unnamed: C1.2, C2.2, RV1.2
unnamed: C2.1, J_OUT_1.P$1_TIP, U1.3
unnamed: D1.2, R_LED_1.1
unnamed: J_CV_1.P$1_TIP, R_LED_1.2, R_VAC_1.2
unnamed: J_IN_1.P$1_TIP, U1.5
unnamed: R_VAC_1.1, U1.2
